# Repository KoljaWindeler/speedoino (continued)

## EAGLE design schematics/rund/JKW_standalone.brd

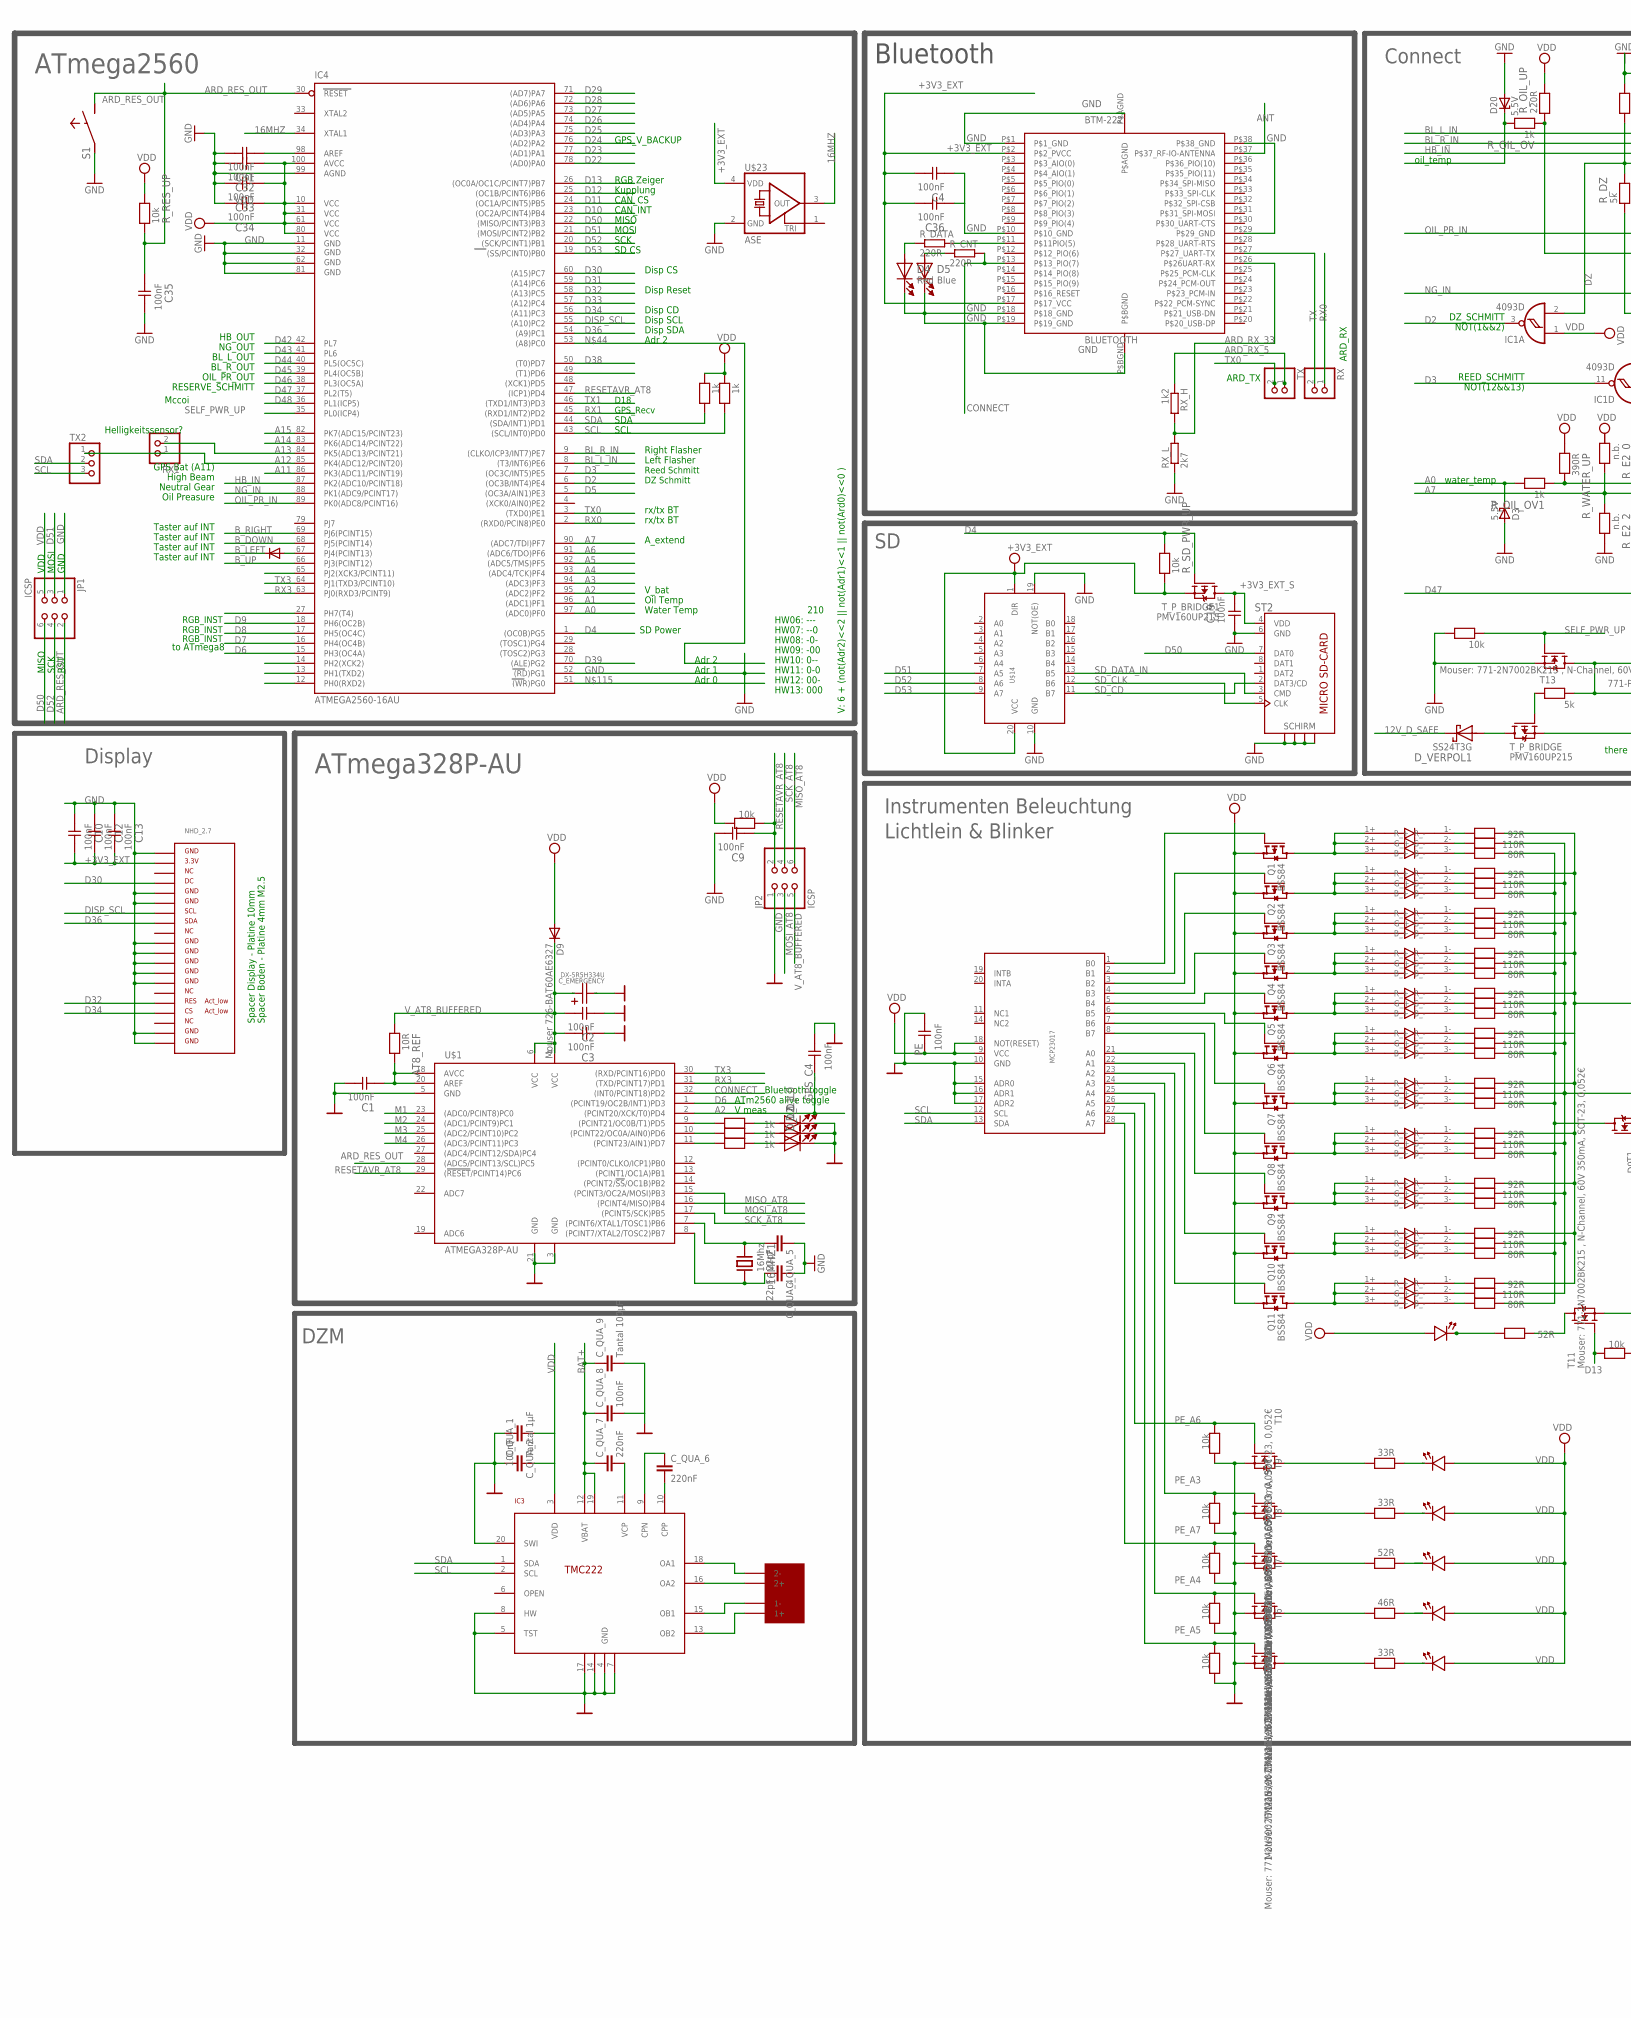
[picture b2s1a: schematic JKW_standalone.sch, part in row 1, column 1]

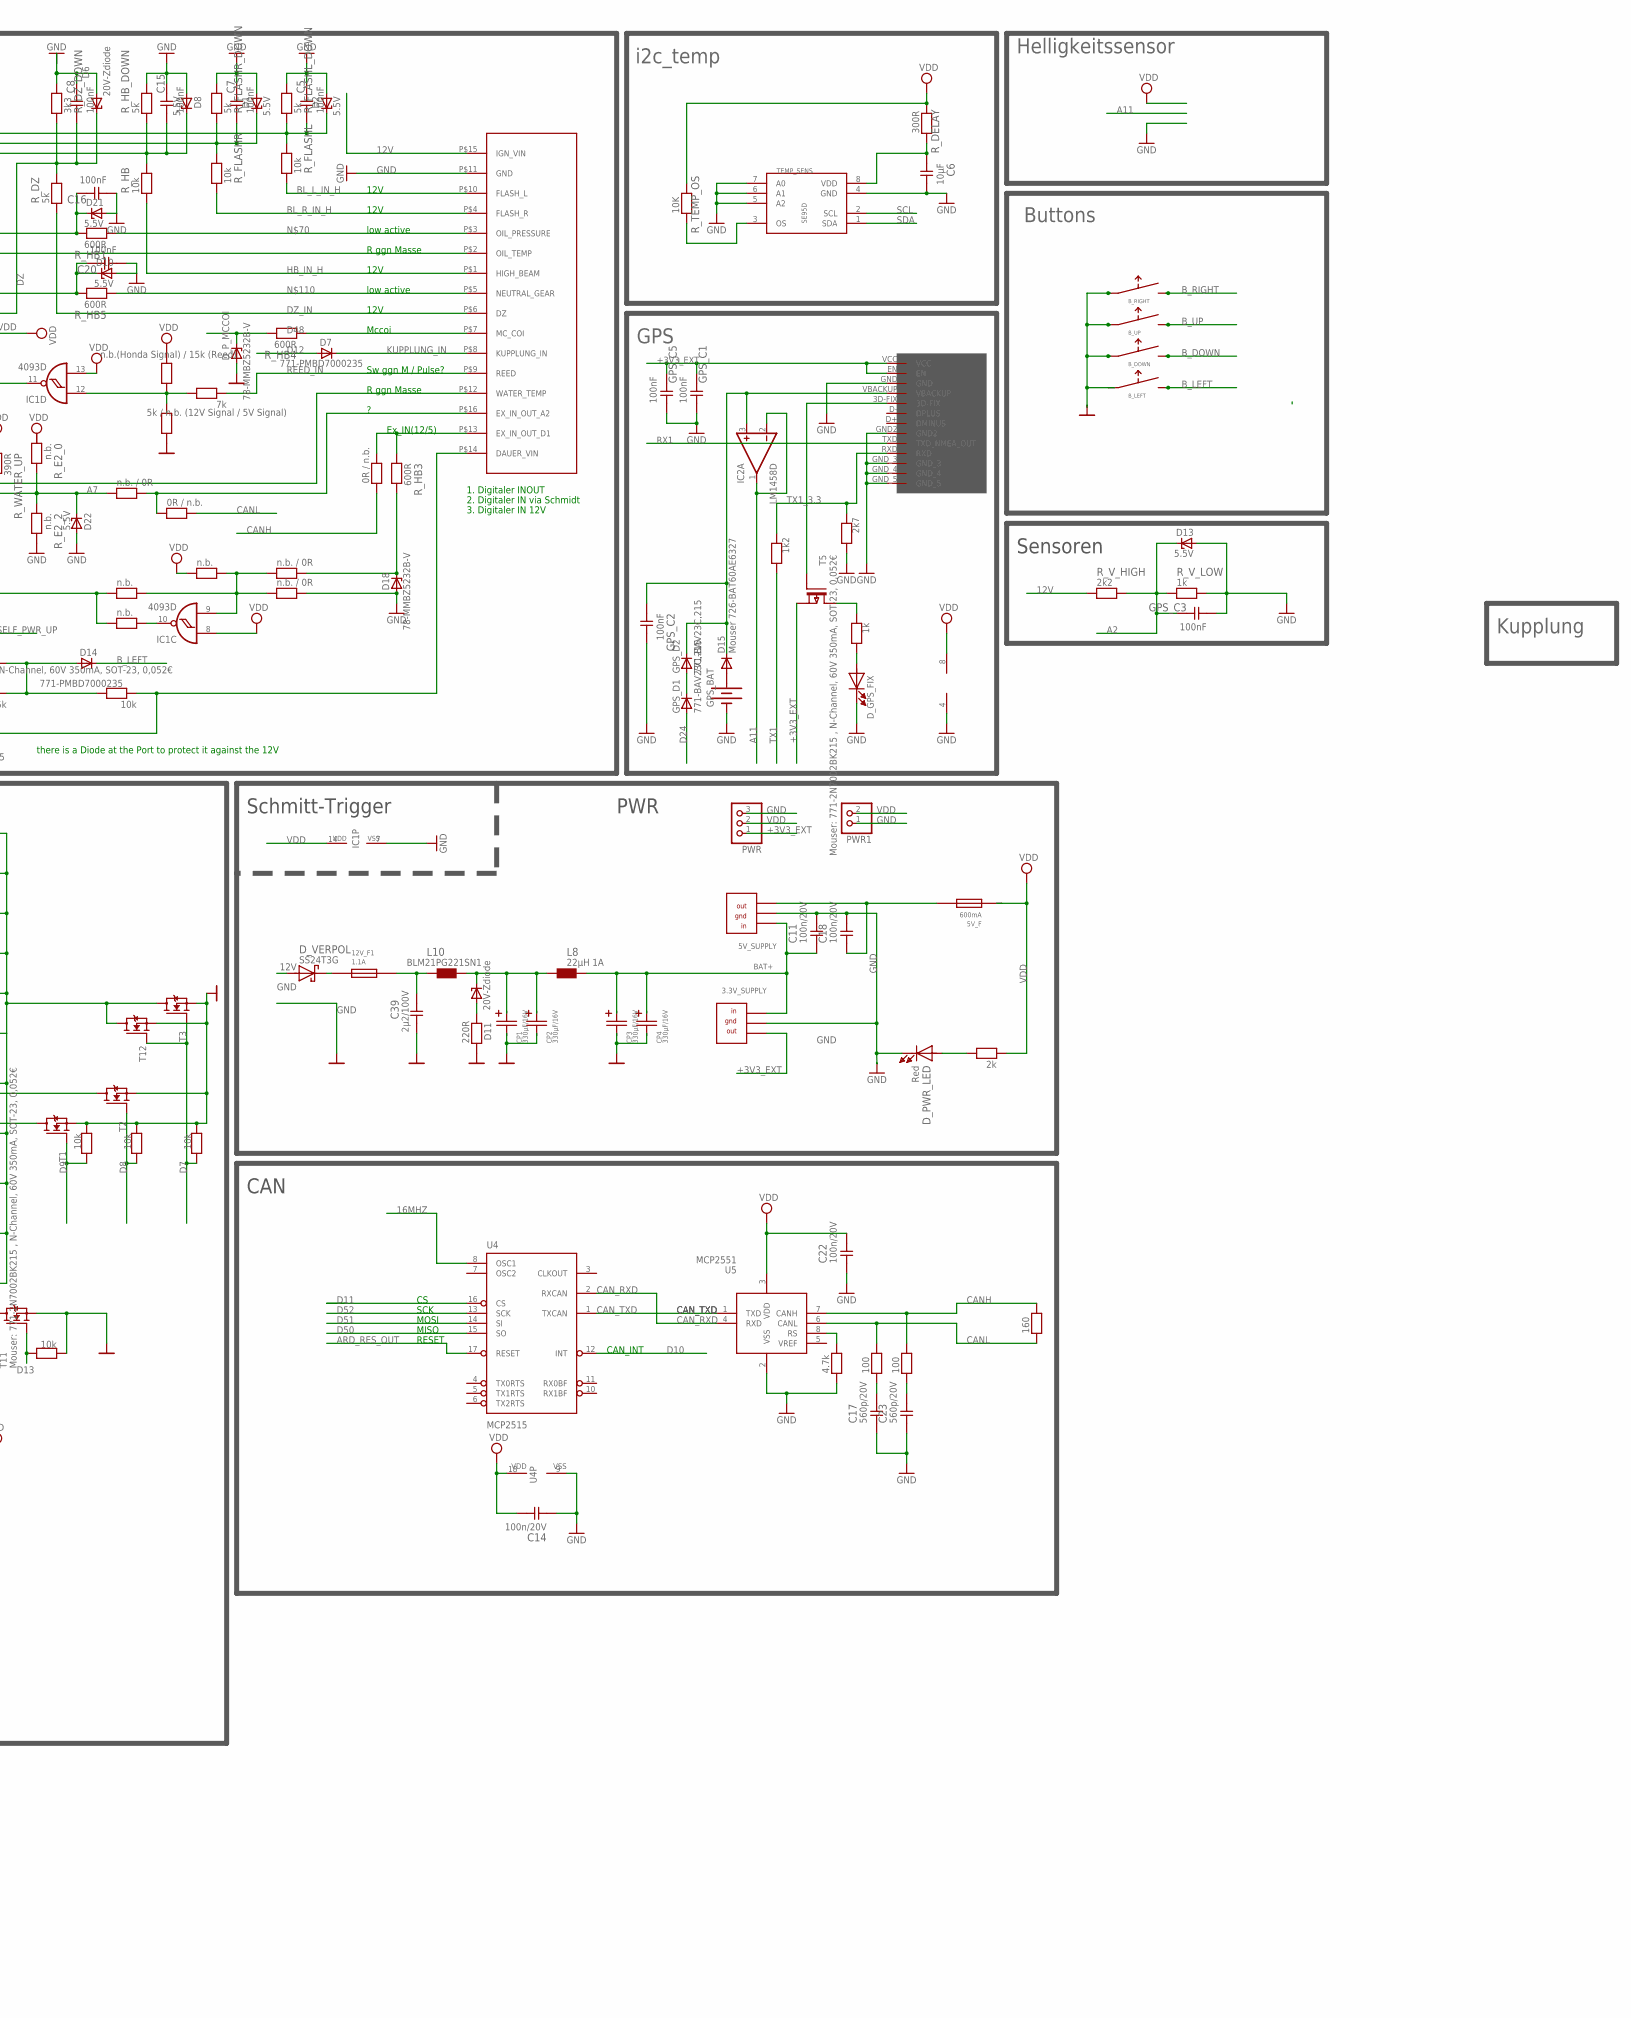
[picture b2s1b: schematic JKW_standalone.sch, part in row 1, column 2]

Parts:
3.3V_SUPPLY: OKI78SR3.31.5WHC; OKI-78SR
5V_F: 600mA; POLY_FUSE
5V_SUPPLY: OKI78SR51.5W36HC; OKI-78SR
12V_F1: 1.1A; POLY_FUSE
16MHZ1: 16Mhz; XT-HC49S-SMD
AT8_REF: 10R; 0805
BLUETOOTH: BTM-222
B_DOWN: SMD_TASTER_MIT_KAPPE; SMD_DRUCKTASTER
B_LEFT: SMD_TASTER_MIT_KAPPE; SMD_DRUCKTASTER
B_RIGHT: SMD_TASTER_MIT_KAPPE; SMD_DRUCKTASTER
B_UP: SMD_TASTER_MIT_KAPPE; SMD_DRUCKTASTER
C1, C2, C3, C4, C5, C7, C8, C9, C10, C12, C13, C15, C16, C19, C20, C31, C32, C33, C34, C35, C36: 100nF; 0805
C6: 10µF; 0805
C11, C14, C18, C22: 100n/20V; 0805
C17, C23: 560p/20V; 0805
C39: 2µ2/100V; 0805
CP1, CP2, CP3, CP4: 330µF/16V; SMD/SMT_6.6/6.6
C_EMERGENCY: DX-5R5H334U; GOLDCAP
C_QUA_1: Tantal 1µF; C0805
C_QUA_2, C_QUA_8: 100nF; C0805
C_QUA_4, C_QUA_5: 22pF; C0805
C_QUA_6, C_QUA_7: 220nF; C0805
C_QUA_9: Tantal 100µF; C0805
D1, D2, D3, D8, D10, D13, D20, D21, D22: 5.5V; SOT23
D4: Red; LED-0805
D5: Blue; LED-0805
D6, D11: 20V-Zdiode; SOT23
D7, D12, D14: 771-PMBD7000235; SOT23
D9, D15: Mouser 726-BAT60AE6327; SOD323-W
D18: 78-MMBZ5232B-V; SOT23
D_GPS_FIX: Red; LED-0805
D_GR_BLR: PLCC4_LED; PLCC-4
D_GR_N: PLCC4_LED; PLCC-4
D_L0, D_L1, D_L2: LED0805; LED-0805
D_PWR_LED: Red; LED-0805
D_P_MCCOI: 78-MMBZ5232B-V; SOT23
D_VERPOL, D_VERPOL1: SS24T3G; SMB
GPS: MT3329
GPS_BAT: F_908642; BATTCON_12MM
GPS_C1, GPS_C2, GPS_C3, GPS_C4, GPS_C5: 100nF; 0805
GPS_D1, GPS_D2: 771-BAV23C,215; SOT23
IC1: 4093D; SO14
IC2: LM1458D; SO08
IC3: TMC222; SOIC20
IC4: ATMEGA2560-16AU; TQFP100
JP1, JP2: ICSP; 2X03
L8: 22µH 1A; L-PD54
L10: BLM21PG221SN1; 0805+603
NHD_2.7: NHD_2.7_SOLO_RO
PE: 100nF; 0805
PWR: PINHD-1X3; 1X03
PWR1: PINHD-1X2; 1X02
Q1, Q2, Q3, Q4, Q5, Q6, Q7, Q8, Q9, Q10, Q11: BSS84; SOT23
R1: 160; 0805
R10, R12: 100; 0805
R13: 4.7k; 0805
RGB_1, RGB_2, RGB_3, RGB_4, RGB_5, RGB_6, RGB_7, RGB_8, RGB_9, RGB_10, RGB_11: RGB_LED; PLCC-6
RX, RX1: PINHD-1X2; 1X02
RX_H: 1k2; M0805
RX_L: 2k7; M0805
R_BL_L: 33R; 0805
R_BL_R: 33R; 0805
R_B_LED_1, R_B_LED_2, R_B_LED_3, R_B_LED_4, R_B_LED_5, R_B_LED_6, R_B_LED_7, R_B_LED_8, R_B_LED_9, R_B_LED_10, R_B_LED_11: 80R; 0805
R_B_LED_12, R_B_LED_13, R_B_LED_14, R_B_LED_15, R_B_LED_16, R_B_LED_17, R_B_LED_18, R_B_LED_19, R_B_LED_20: 10k; 0805
R_CNT: 220R; M0805
R_DATA: 220R; M0805
R_DEAKT_DAUER_P, R_DEAKT_DAUER_P1: 10k; 0805
R_DEAKT_DAUER_P2: 5k; 0805
R_DELAY: 300R; 0805
R_DZ: 5k; 0805
R_DZ_DOWN: 3k3; 0805
R_E1_0, R_E1_2, R_E1_4, R_E2_0, R_E2_2: n.b.; 0805
R_E1_1, R_E1_3, R_E2_1: n.b. / 0R; 0805
R_E2_3, R_E2_4: 0R / n.b.; 0805
R_FLASHL: 10k; 0805
R_FLASHL_DOWN: 5k; 0805
R_FLASHR: 10k; 0805
R_FLASHR_DOWN: 5k; 0805
R_GPS_LED: 1k; 0805
R_GR_BL_L: PLCC4_LED; PLCC-4
R_G_LED_1, R_G_LED_2, R_G_LED_3, R_G_LED_4, R_G_LED_5, R_G_LED_6, R_G_LED_7, R_G_LED_8, R_G_LED_9, R_G_LED_10, R_G_LED_11: 110R; 0805
R_HB: 10k; 0805
R_HB1, R_HB3, R_HB4, R_HB5: 600R; 0805
R_HB_DOWN: 5k; 0805
R_HIGHB: 46R; 0805
R_L0, R_L1, R_L2: 1k; 0805
R_L3: 10k; 0805
R_LED_5V: 2k; 0805
R_N: 33R; 0805
R_OIL: 52R; 0805
R_OIL_OV, R_OIL_OV1: 1k; 0805
R_OIL_UP: 220R; 0805
R_REED: 7k; 0805
R_REED_DOWN: 5k / n.b. (12V Signal / 5V Signal); 0805
R_REED_UP: n.b.(Honda Signal) / 15k (Reed); 0805
R_RES_UP: 10k; 0805
R_R_LED_0: 52R; 0805
R_R_LED_1, R_R_LED_2, R_R_LED_3, R_R_LED_4, R_R_LED_5, R_R_LED_6, R_R_LED_7, R_R_LED_8, R_R_LED_9, R_R_LED_10, R_R_LED_11: 92R; 0805
R_R_LED_12: 220R; 0805
R_SCL_UP: 1k; 0805
R_SDA_UP: 1k; 0805
R_SD_PWR_UP: 10k; 0805
R_TEMP_OS: 10K; 0805
R_TX_DOWN: 2k7; 0805
R_TX_UP: 1k2; 0805
R_V_HIGH: 2k2; 0805
R_V_LOW: 1k; 0805
R_WATER_UP: 390R; 0805
S1: SW-TASTERECO-DIAGONAL; SW-ECO
SPEEDOSTECKER: SPEEDOSTECKER
ST2: SD_MICRO
STEPPER: STEPPER
T1, T2, T3, T6, T7, T8, T9, T10, T11, T12, T13: Mouser: 771-2N7002BK215 , N-Channel, 60V 350mA, S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; SOT23
T5: Mouser: 771-2N7002BK215 , N-Channel, 60V 350mA, S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; SOT-23
TEMP_SENS: SE95D; SOIC8
TX: PINHD-1X2; 1X02
TX2: PINHD-1X3; 1X03
T_P_BRIDGE, T_P_BRIDGE1: PMV160UP215; SOT23
U4: MCP2515; SO-18W
U5: MCP2551; SO-08M
U$1: ATMEGA328P-AU; TQFP8
U$3: CLM4B-BKW-CTBVA363; PLCC-4
U$11, U$22: CLM4B-RKW-CWAXBAA3; PLCC-4
U$14: 74LVC_LVCH245A; TSSOP20
U$19: MCP23017; SOIC28
U$23: ASE

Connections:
3D-FIX: GPS.3D-FIX, T5.1 (G)
12V: D_VERPOL.A, R_V_HIGH.1, SPEEDOSTECKER.P$15 (IGN_VIN)
12V_D_SAFE: 12V_F1.P$1, D_VERPOL.K, D_VERPOL1.K
12V_PERMANENT: R_DEAKT_DAUER_P.1, SPEEDOSTECKER.P$14 (DAUER_VIN), T_P_BRIDGE.2 (S)
12V_SAFE: 12V_F1.P$2, C39.1, L10.1
16MHZ: IC4.34 (XTAL1), U4.8 (OSC1), U$23.3 (OUT)
+3V3_EXT: 3.3V_SUPPLY.OUT, BLUETOOTH.P$2 (P$2_PVCC), BLUETOOTH.P$17 (P$17_VCC), C4.2, C10.2, C12.2, C13.2, C36.2, GPS.EN, GPS.VCC, GPS_C1.2, GPS_C5.2, NHD_2.7.VDD0 (VDD), PWR.1, R_SD_PWR_UP.1, T5.2 (S), T_P_BRIDGE1.2 (S), U$14.1 (DIR), U$14.20 (VCC)
+3V3_EXT_S: C19.2, ST2.4 (VDD), T_P_BRIDGE1.3 (D)
A0: D3.3 (C), IC4.97 ((ADC0)PF0), R_OIL_OV1.2
A1: D20.3 (C), IC4.96 ((ADC1)PF1), R_OIL_OV.2
A2: D13.3 (C), GPS_C3.2, GPS_C4.2, IC4.95 ((ADC2)PF2), R_V_HIGH.2, R_V_LOW.1, U$1.2 ((PCINT20/XCK/T0)PD4)
A3: IC4.94 ((ADC3)PF3)
A4: IC4.93 ((ADC4/TCK)PF4)
A5: IC4.92 ((ADC5/TMS)PF5)
A6: IC4.91 ((ADC6/TDO)PF6)
A7: D22.3 (C), IC4.90 ((ADC7/TDI)PF7), R_E2_0.2, R_E2_1.2, R_E2_2.1
A11: IC2.1 (OUT), IC2.2 (-IN), IC4.86 (PK3(ADC11/PCINT19))
A12: IC4.85 (PK4(ADC12/PCINT20)), RX1.1, TX2.1
A13: IC4.84 (PK5(ADC13/PCINT21)), RX1.2
A14: IC4.83 (PK6(ADC14/PCINT22))
A15: IC4.82 (PK7(ADC15/PCINT23))
ANT: BLUETOOTH.P$37 (P$37_RF-IO-ANTENNA)
ARD_RES_OUT: C35.1, IC4.30 (RESET), JP1.2, R_RES_UP.1, S1.4 (2), U4.17 (RESET), U$1.28 ((ADC5/PCINT13/SCL)PC5)
ARD_RX_5: RX_H.1, TX.1
ARD_RX_33: BLUETOOTH.P$26 (P$26UART-RX), RX_H.2, RX_L.2
BAT+: 3.3V_SUPPLY.IN, 5V_SUPPLY.IN, C11.1, CP3.POS (PLUS), CP4.POS (PLUS), C_QUA_7.1, C_QUA_8.1, C_QUA_9.1, IC3.12 (VBAT), IC3.19 (VBAT2), L8.2
BLUE_INSTR: R_B_LED_1.2, R_B_LED_2.2, R_B_LED_3.2, R_B_LED_4.2, R_B_LED_5.2, R_B_LED_6.2, R_B_LED_7.2, R_B_LED_8.2, R_B_LED_9.2, R_B_LED_10.2, R_B_LED_11.2, T1.3 (D)
BL_L_IN: C5.1, D2.3 (C), IC4.8 ((T3/INT6)PE6), R_FLASHL.2, R_FLASHL_DOWN.1
BL_L_IN_H: R_FLASHL.1, SPEEDOSTECKER.P$10 (FLASH_L)
BL_R_IN: C7.1, D1.3 (C), IC4.9 ((CLKO/ICP3/INT7)PE7), R_FLASHR.2, R_FLASHR_DOWN.1
BL_R_IN_H: R_FLASHR.1, SPEEDOSTECKER.P$4 (FLASH_R)
B_DOWN: B_DOWN.OUT, IC4.68 (PJ5(PCINT14))
B_LEFT: B_LEFT.OUT, D12.3 (C), D14.3 (C)
B_RIGHT: B_RIGHT.OUT, IC4.69 (PJ6(PCINT15))
B_UP: B_UP.OUT, IC4.66 (PJ3(PCINT12))
CANH: R1.2, R12.2, R_E2_4.2, U5.7 (CANH)
CANL: R1.1, R10.2, R_E2_3.1, U5.6 (CANL)
CAN_RXD: U4.2 (RXCAN), U5.4 (RXD)
CAN_TXD: U4.1 (TXCAN), U5.1 (TXD)
CONNECT: BLUETOOTH.P$13 (P$13_PIO(7)), R_CNT.2, U$1.32 ((INT0/PCINT18)PD2)
D2: IC1.3 (O), IC4.6 ((OC3B/INT4)PE4)
D3: IC1.11 (O), IC4.7 ((OC3C/INT5)PE5)
D4: IC4.1 ((OC0B)PG5), R_SD_PWR_UP.2, T_P_BRIDGE1.1 (G)
D5: IC4.5 ((OC3A/AIN1)PE3)
D6: IC4.15 (PH3(OC4A)), U$1.1 ((PCINT19/OC2B/INT1)PD3)
D7: IC4.16 (PH4(OC4B)), R_B_LED_15.1, T3.1 (G), T12.1 (G)
D8: IC4.17 (PH5(OC4C)), R_B_LED_14.1, T2.1 (G)
D9: IC4.18 (PH6(OC2B)), R_B_LED_13.1, T1.1 (G)
D10: IC4.23 ((OC2A/PCINT4)PB4), U4.12 (INT)
D11: IC4.24 ((OC1A/PCINT5)PB5), U4.16 (CS)
D12: D7.1 (A), IC4.25 ((OC1B/PCINT6)PB6)
D13: IC4.26 ((OC0A/OC1C/PCINT7)PB7), R_B_LED_12.1, T11.1 (G)
D22: IC4.78 ((AD0)PA0)
D23: IC4.77 ((AD1)PA1)
D24: GPS_D1.1 (A), IC4.76 ((AD2)PA2)
D25: IC4.75 ((AD3)PA3)
D26: IC4.74 ((AD4)PA4)
D27: IC4.73 ((AD5)PA5)
D28: IC4.72 ((AD6)PA6)
D29: IC4.71 ((AD7)PA7)
D30: IC4.60 ((A15)PC7), NHD_2.7.DC
D31: IC4.59 ((A14)PC6)
D32: IC4.58 ((A13)PC5), NHD_2.7.RES
D33: IC4.57 ((A12)PC4)
D34: IC4.56 ((A11)PC3), NHD_2.7.CS
D36: IC4.54 ((A9)PC1), NHD_2.7.SDIN (SDA)
D38: IC4.50 ((T0)PD7)
D39: IC4.70 ((ALE)PG2)
D42: IC4.42 (PL7)
D43: IC4.41 (PL6)
D44: IC4.40 (PL5(OC5C))
D45: IC4.39 (PL4(OC5B))
D46: IC4.38 (PL3(OC5A))
D47: IC4.37 (PL2(T5)), R_E1_2.2, R_E1_4.2
D48: D_P_MCCOI.3 (C), IC4.36 (PL1(ICP5)), R_HB4.2
D50: IC4.22 ((MISO/PCINT3)PB3), JP1.6, ST2.7 (DAT0), U4.15 (SO)
D51: IC4.21 ((MOSI/PCINT2)PB2), JP1.3, U4.14 (SI), U$14.7 (A5)
D52: IC4.20 ((SCK/PCINT1)PB1), JP1.4, U4.13 (SCK), U$14.8 (A6)
D53: IC4.19 ((SS/PCINT0)PB0), U$14.9 (A7)
DISP_SCL: IC4.55 ((A10)PC2), NHD_2.7.SCLK (SCL)
DZ: C8.1, D6.3 (C), IC1.2 (I1), R_DZ.2, R_DZ_DOWN.1
DZ_IN: R_DZ.1, SPEEDOSTECKER.P$6 (DZ)
GND: 3.3V_SUPPLY.GND, 5V_SUPPLY.GND, BLUETOOTH.P$1 (P$1_GND), BLUETOOTH.P$10 (P$10_GND), BLUETOOTH.P$18 (P$18_GND), BLUETOOTH.P$19 (P$19_GND), BLUETOOTH.P$29 (P$29_GND), BLUETOOTH.P$38 (P$38_GND), BLUETOOTH.P$AGND, BLUETOOTH.P$BGND, B_DOWN.IN, B_DOWN.IN2 (IN), B_LEFT.IN, B_LEFT.IN2 (IN), B_RIGHT.IN, B_RIGHT.IN2 (IN), B_UP.IN, B_UP.IN2 (IN), C1.2, C2.1, C3.1, C4.1, C5.2, C6.2, C7.2, C8.2, C9.2, C10.1, C11.2, C12.1, C13.1, C14.1, C15.2, C16.1, C17.1, C18.2, C19.1, C20.1, C22.1, C23.1, C31.2, C32.2, C33.2, C34.2, C35.2, C36.1, C39.2, CP1.NEG (GND), CP2.NEG (GND), CP3.NEG (GND), CP4.NEG (GND), C_EMERGENCY.MINUS (GND), C_QUA_1.1, C_QUA_2.2, C_QUA_4.1, C_QUA_5.1, C_QUA_8.2, C_QUA_9.2, D1.1 (A), D2.1 (A), D3.1 (A), D4.2 (K), D5.2 (K), D6.1 (A), D8.1 (A), D10.1 (A), D13.1 (A), D18.1 (A), D20.1 (A), D21.1 (A), D22.1 (A), D_GPS_FIX.2 (K), D_L0.2 (K), D_L1.2 (K), D_L2.2 (K), D_PWR_LED.2 (K), D_P_MCCOI.1 (A), GPS.GND, GPS.GND2, GPS.GND_3, GPS.GND_4, GPS.GND_5, GPS_BAT.GND (-), GPS_C1.1, GPS_C2.2, GPS_C3.1, GPS_C4.1, GPS_C5.1, IC1.7 (VSS), IC2.4 (V-), IC3.4 (GND), IC3.5 (TST), IC3.7 (GND2), IC3.8 (HW), IC3.14 (GND3), IC3.17 (GND4), IC3.20 (SWI), IC4.11 (GND), IC4.32 (GND1), IC4.52 ((RD)PG1), IC4.62 (GND2), IC4.81 (GND3), IC4.99 (AGND), JP1.1, JP2.1, NHD_2.7.GND0 (GND), NHD_2.7.GND1 (GND2), NHD_2.7.GND2 (GND3), NHD_2.7.GND3 (GND4), NHD_2.7.GND4 (GND5), NHD_2.7.GND5 (GND6), NHD_2.7.GND6 (GND7), NHD_2.7.GND7 (GND8), NHD_2.7.GND8 (GND9), NHD_2.7.GND9 (GND10), PE.1, PWR.3, PWR1.1, R13.1, RX_L.1, R_B_LED_12.2, R_B_LED_13.2, R_B_LED_14.2, R_B_LED_15.2, R_B_LED_16.1, R_B_LED_17.1, R_B_LED_18.1, R_B_LED_19.1, R_B_LED_20.1, R_DEAKT_DAUER_P1.2, R_DZ_DOWN.2, R_E1_3.1, R_E2_2.2, R_FLASHL_DOWN.2, R_FLASHR_DOWN.2, R_HB_DOWN.2, R_REED_DOWN.2, R_R_LED_12.1, R_TX_DOWN.2, R_V_LOW.2, S1.1, SPEEDOSTECKER.P$11 (GND), ST2.6 (GND), ST2.GND (SCHIRM1), ST2.GND2 (SCHIRM2), ST2.GND3 (SCHIRM3), ST2.GND4 (SCHIRM), T1.2 (S), T2.2 (S), T3.2 (S), T6.2 (S), T7.2 (S), T8.2 (S), T9.2 (S), T10.2 (S), T11.2 (S), T12.2 (S), T13.2 (S), TEMP_SENS.4 (GND), TEMP_SENS.5 (A2), TEMP_SENS.6 (A1), TEMP_SENS.7 (A0), U4.9 (VSS), U5.2 (VSS), U$1.3 (GND), U$1.5 (GND), U$1.21 (GND), U$14.10 (GND), U$14.19 (NOT(OE)), U$19.10 (GND), U$19.15 (ADR0), U$19.16 (ADR1), U$19.17 (ADR2), U$23.2 (GND)
GREEN_INSTR: R_G_LED_1.2, R_G_LED_2.2, R_G_LED_3.2, R_G_LED_4.2, R_G_LED_5.2, R_G_LED_6.2, R_G_LED_7.2, R_G_LED_8.2, R_G_LED_9.2, R_G_LED_10.2, R_G_LED_11.2, T2.3 (D)
HB_IN: C15.1, D8.3 (C), IC4.87 (PK2(ADC10/PCINT18)), R_HB.2, R_HB_DOWN.1
HB_IN_H: R_HB.1, SPEEDOSTECKER.P$1 (HIGH_BEAM)
KUPPLUNG_IN: D7.3 (C), SPEEDOSTECKER.P$8 (KUPPLUNG_IN)
M1: U$1.23 ((ADC0/PCINT8)PC0)
M2: U$1.24 ((ADC1/PCINT9)PC1)
M3: U$1.25 ((ADC2/PCINT10)PC2)
M4: U$1.26 ((ADC3/PCINT11)PC3)
MISO_AT8: JP2.6, U$1.16 ((PCINT4/MISO)PB4)
MOSI_AT8: JP2.3, U$1.15 ((PCINT3/OC2A/MOSI)PB3)
N999: R_OIL_OV.1, R_OIL_UP.1, SPEEDOSTECKER.P$2 (OIL_TEMP)
unnamed: CP1.POS (PLUS), CP2.POS (PLUS), D11.3 (C), L8.1, L10.2
unnamed: AT8_REF.2, C1.1, U$1.18 (AVCC), U$1.20 (AREF)
unnamed: C6.1, R_DELAY.1, TEMP_SENS.8 (VDD)
unnamed: D5.1 (A), R_CNT.1
unnamed: RGB_5.3- (B_-), R_B_LED_4.1
unnamed: RGB_5.2- (G_-), R_G_LED_4.1
unnamed: RGB_5.1- (R_-), R_R_LED_4.1
unnamed: D_PWR_LED.1 (A), R_LED_5V.2
unnamed: RGB_6.3- (B_-), R_B_LED_5.1
unnamed: D15.A, GPS_BAT.PWR@1 (+)
unnamed: D4.1 (A), R_DATA.1
unnamed: Q11.3 (D), RGB_11.1+ (R_+), RGB_11.2+ (G_+), RGB_11.3+ (B_+)
unnamed: R_L2.1, U$1.11 ((PCINT23/AIN1)PD7)
unnamed: D_GPS_FIX.1 (A), R_GPS_LED.2
unnamed: R_R_LED_0.1, U$22.P$4 (CATHODE)
unnamed: R_GPS_LED.1, T5.3 (D)
unnamed: R_L1.1, U$1.10 ((PCINT22/OC0A/AIN0)PD6)
unnamed: 5V_F.P$2, 5V_SUPPLY.OUT, C18.1
unnamed: R_L0.1, U$1.9 ((PCINT21/OC0B/T1)PD5)
unnamed: RGB_6.2- (G_-), R_G_LED_5.1
unnamed: RGB_6.1- (R_-), R_R_LED_5.1
unnamed: Q10.3 (D), RGB_10.1+ (R_+), RGB_10.2+ (G_+), RGB_10.3+ (B_+)
unnamed: R_DEAKT_DAUER_P2.2, T_P_BRIDGE.1 (G)
unnamed: R_OIL.1, U$11.P$4 (CATHODE)
unnamed: Q9.3 (D), RGB_1.1+ (R_+), RGB_1.2+ (G_+), RGB_1.3+ (B_+)
unnamed: RGB_7.3- (B_-), R_B_LED_6.1
unnamed: R_HIGHB.1, U$3.P$4 (CATHODE)
unnamed: RGB_7.2- (G_-), R_G_LED_6.1
unnamed: RGB_7.1- (R_-), R_R_LED_6.1
unnamed: R_BL_L.2, T10.3 (D)
unnamed: R_BL_R.2, T9.3 (D)
unnamed: IC3.18 (OA1), STEPPER.2-
unnamed: IC3.16 (OA2), STEPPER.2+
unnamed: C31.1, IC4.98 (AREF)
unnamed: IC1.9 (I1), R_E1_0.1, R_E1_1.2, R_E1_2.1, R_E1_3.2
unnamed: R_HIGHB.2, T7.3 (D)
unnamed: IC1.10 (O), R_E1_4.1
unnamed: D12.1 (A), IC4.67 (PJ4(PCINT13))
unnamed: R_E2_4.1, R_HB3.1, SPEEDOSTECKER.P$13 (EX_IN_OUT_D1)
unnamed: R_E2_1.1, R_E2_3.2, SPEEDOSTECKER.P$16 (EX_IN_OUT_A2)
unnamed: D_VERPOL1.A, T_P_BRIDGE.3 (D)
unnamed: C17.2, R10.1
unnamed: GPS_D1.3 (C), GPS_D2.1 (A)
unnamed: IC3.13 (OB2), STEPPER.1+
unnamed: RGB_4.1- (R_-), R_R_LED_3.1
unnamed: RGB_4.2- (G_-), R_G_LED_3.1
unnamed: RGB_4.3- (B_-), R_B_LED_3.1
unnamed: RGB_3.1- (R_-), R_R_LED_2.1
unnamed: RGB_3.2- (G_-), R_G_LED_2.1
unnamed: RGB_3.3- (B_-), R_B_LED_2.1
unnamed: RGB_2.1- (R_-), R_R_LED_1.1
unnamed: RGB_2.2- (G_-), R_G_LED_1.1
unnamed: RGB_2.3- (B_-), R_B_LED_1.1
unnamed: R_BL_L.1, R_GR_BL_L.P$4 (CATHODE)
unnamed: 16MHZ1.1, C_QUA_5.2, U$1.7 ((PCINT6/XTAL1/TOSC1)PB6)
unnamed: RGB_11.1- (R_-), R_R_LED_7.1
unnamed: 16MHZ1.2, C_QUA_4.2, U$1.8 ((PCINT7/XTAL2/TOSC2)PB7)
unnamed: D_GR_BLR.P$4 (CATHODE), R_BL_R.1
unnamed: R_N.2, T6.3 (D)
unnamed: R_OIL.2, T8.3 (D)
unnamed: D_GR_N.P$4 (CATHODE), R_N.1
unnamed: R_HB1.1, SPEEDOSTECKER.P$3 (OIL_PRESSURE)
unnamed: R_R_LED_0.2, T11.3 (D)
unnamed: RGB_11.2- (G_-), R_G_LED_7.1
unnamed: RGB_11.3- (B_-), R_B_LED_7.1
unnamed: RGB_10.1- (R_-), R_R_LED_8.1
unnamed: RGB_10.2- (G_-), R_G_LED_8.1
unnamed: RGB_10.3- (B_-), R_B_LED_8.1
unnamed: RGB_9.1- (R_-), R_R_LED_9.1
unnamed: RGB_9.2- (G_-), R_G_LED_9.1
unnamed: RGB_9.3- (B_-), R_B_LED_9.1
unnamed: RGB_8.1- (R_-), R_R_LED_10.1
unnamed: RGB_8.2- (G_-), R_G_LED_10.1
unnamed: RGB_8.3- (B_-), R_B_LED_10.1
unnamed: RGB_1.1- (R_-), R_R_LED_11.1
unnamed: RGB_1.2- (G_-), R_G_LED_11.1
unnamed: RGB_1.3- (B_-), R_B_LED_11.1
unnamed: Q8.3 (D), RGB_8.1+ (R_+), RGB_8.2+ (G_+), RGB_8.3+ (B_+)
unnamed: Q7.3 (D), RGB_9.1+ (R_+), RGB_9.2+ (G_+), RGB_9.3+ (B_+)
unnamed: Q1.3 (D), RGB_7.1+ (R_+), RGB_7.2+ (G_+), RGB_7.3+ (B_+)
unnamed: C23.2, R12.1
unnamed: D18.3 (C), R_E1_1.1, R_HB3.2
unnamed: R_TEMP_OS.1, TEMP_SENS.3 (OS)
unnamed: R_HB4.1, SPEEDOSTECKER.P$7 (MC_COI)
unnamed: Q2.3 (D), RGB_6.1+ (R_+), RGB_6.2+ (G_+), RGB_6.3+ (B_+)
unnamed: Q3.3 (D), RGB_5.1+ (R_+), RGB_5.2+ (G_+), RGB_5.3+ (B_+)
unnamed: Q4.3 (D), RGB_4.1+ (R_+), RGB_4.2+ (G_+), RGB_4.3+ (B_+)
unnamed: Q6.3 (D), RGB_2.1+ (R_+), RGB_2.2+ (G_+), RGB_2.3+ (B_+)
unnamed: Q5.3 (D), RGB_3.1+ (R_+), RGB_3.2+ (G_+), RGB_3.3+ (B_+)
unnamed: Q1.1 (G), U$19.1 (B0)
unnamed: Q2.1 (G), U$19.2 (B1)
unnamed: Q3.1 (G), U$19.3 (B2)
unnamed: Q4.1 (G), U$19.4 (B3)
unnamed: Q5.1 (G), U$19.5 (B4)
unnamed: Q6.1 (G), U$19.6 (B5)
unnamed: Q7.1 (G), U$19.7 (B6)
unnamed: Q8.1 (G), U$19.8 (B7)
unnamed: Q9.1 (G), U$19.21 (A0)
unnamed: Q10.1 (G), U$19.22 (A1)
unnamed: Q11.1 (G), U$19.23 (A2)
unnamed: D11.1 (A), R_R_LED_12.2
unnamed: R_HB5.1, SPEEDOSTECKER.P$5 (NEUTRAL_GEAR)
unnamed: R_OIL_OV1.1, R_WATER_UP.2, SPEEDOSTECKER.P$12 (WATER_TEMP)
unnamed: R13.2, U5.8 (RS)
unnamed: IC3.15 (OB1), STEPPER.1-
unnamed: C_QUA_6.2, IC3.10 (CPP)
unnamed: C_QUA_6.1, IC3.9 (CPN)
unnamed: C_QUA_7.2, IC3.11 (VCP)
NET12: D14.1 (A), R_DEAKT_DAUER_P.2, R_DEAKT_DAUER_P2.1, T13.3 (D)
NG_IN: C20.2, D10.3 (C), IC4.88 (PK1(ADC9/PCINT17)), R_HB5.2
OIL_PR_IN: C16.2, D21.3 (C), IC4.89 (PK0(ADC8/PCINT16)), R_HB1.2
P0: D_L0.1 (A), R_L0.2
P1: D_L1.1 (A), R_L1.2
P2: D_L2.1 (A), R_L2.2
PE_A3: R_B_LED_17.2, T9.1 (G), U$19.24 (A3)
PE_A4: R_B_LED_19.2, T7.1 (G), U$19.25 (A4)
PE_A5: R_B_LED_20.2, T6.1 (G), U$19.26 (A5)
PE_A6: R_B_LED_16.2, T10.1 (G), U$19.27 (A6)
PE_A7: R_B_LED_18.2, T8.1 (G), U$19.28 (A7)
RED_INSTR: R_R_LED_1.2, R_R_LED_2.2, R_R_LED_3.2, R_R_LED_4.2, R_R_LED_5.2, R_R_LED_6.2, R_R_LED_7.2, R_R_LED_8.2, R_R_LED_9.2, R_R_LED_10.2, R_R_LED_11.2, T3.3 (D), T12.3 (D)
REED: IC1.12 (I0), R_REED.2, R_REED_DOWN.1, R_REED_UP.2
REED_IN: R_REED.1, SPEEDOSTECKER.P$9 (REED)
RESETAVR_AT8: C9.1, IC4.47 ((ICP1)PD4), JP2.2, R_L3.2, U$1.29 ((!RESET!/PCINT14)PC6)
RX0: IC4.2 ((RXD0/PCIN8)PE0), RX.1
RX1: GPS.TXD (TXD_NMEA_OUT), IC4.45 ((RXD1/INT2)PD2)
RX3: IC4.63 (PJ0(RXD3/PCINT9)), U$1.31 ((TXD/PCINT17)PD1)
SCK_AT8: JP2.4, U$1.17 ((PCINT5/SCK)PB5)
SCL: IC3.2 (SCL), IC4.43 ((SCL/INT0)PD0), R_SCL_UP.2, TEMP_SENS.2 (SCL), TX2.3, U$19.12 (SCL)
SDA: IC3.1 (SDA), IC4.44 ((SDA/INT1)PD1), R_SDA_UP.2, TEMP_SENS.1 (SDA), TX2.2, U$19.13 (SDA)
SD_CD: ST2.2 (DAT3/CD), U$14.11 (B7)
SD_CLK: ST2.5 (CLK), U$14.12 (B6)
SD_DATA_IN: ST2.3 (CMD), U$14.13 (B5)
SELF_PWR_UP: IC4.35 (PL0(ICP4)), R_DEAKT_DAUER_P1.1, T13.1 (G)
TO_DATA_LED: BLUETOOTH.P$11 (P$11PIO(5)), R_DATA.2
TX: BLUETOOTH.P$27 (P$27_UART-TX), RX.2
TX0: IC4.3 ((TXD0)PE1), TX.2
TX1: IC4.46 ((TXD1/INT3)PD3), R_TX_UP.2
TX1_3.3: GPS.RXD, R_TX_DOWN.1, R_TX_UP.1
TX3: IC4.64 (PJ1(TXD3/PCINT10)), U$1.30 ((RXD/PCINT16)PD0)
VDD: 5V_F.P$1, C14.2, C22.2, C32.1, C33.1, C34.1, C_QUA_1.2, C_QUA_2.1, D9.A, D_GR_BLR.P$1 (ANODE), D_GR_BLR.P$2 (ANODE), D_GR_BLR.P$3 (ANODE), D_GR_N.P$1 (ANODE), D_GR_N.P$2 (ANODE), D_GR_N.P$3 (ANODE), IC1.1 (I0), IC1.8 (I0), IC1.13 (I1), IC1.14 (VDD), IC2.8 (V+), IC3.3 (VDD), IC4.10 (VCC), IC4.31 (VCC1), IC4.61 (VCC2), IC4.80 (VCC3), IC4.100 (AVCC), JP1.5, PE.2, PWR.2, PWR1.2, Q1.2 (S), Q2.2 (S), Q3.2 (S), Q4.2 (S), Q5.2 (S), Q6.2 (S), Q7.2 (S), Q8.2 (S), Q9.2 (S), Q10.2 (S), Q11.2 (S), R_DELAY.2, R_E1_0.2, R_GR_BL_L.P$1 (ANODE), R_GR_BL_L.P$2 (ANODE), R_GR_BL_L.P$3 (ANODE), R_L3.1, R_LED_5V.1, R_OIL_UP.2, R_REED_UP.1, R_RES_UP.2, R_SCL_UP.1, R_SDA_UP.1, R_TEMP_OS.2, R_WATER_UP.1, U4.18 (VDD), U5.3 (VDD), U$3.P$1 (ANODE), U$3.P$2 (ANODE), U$3.P$3 (ANODE), U$11.P$1 (ANODE), U$11.P$2 (ANODE), U$11.P$3 (ANODE), U$19.9 (VCC), U$19.18 (NOT(RESET)), U$22.P$1 (ANODE), U$22.P$2 (ANODE), U$22.P$3 (ANODE), U$23.4 (VDD)
V_AT8_BUFFERED: AT8_REF.1, C2.2, C3.2, C_EMERGENCY.PLUS, D9.C, JP2.5, U$1.4 (VCC), U$1.6 (VCC)
V_BAT: D15.C, GPS.VBACKUP, GPS_C2.1, GPS_D2.3 (C), IC2.3 (+IN)

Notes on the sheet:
Schmitt-Trigger
PWR
Sensoren
Bluetooth
Buttons
MOSI
SCK
MISO
SDA
SCL
DZ_SCHMITT
REED_SCHMITT
oil_temp
ATmega2560
D18
GND
VDD
RST
ATm2560 alive toggle
ARD_RX
ARD_TX
i2c_temp
ATmega328P-AU
Lichtlein & Blinker
Instrumenten Beleuchtung
RGB_INST
Reed Schmitt
DZ Schmitt
GPS
GPS_Recv
Display
DZM
Oil Temp
rx/tx BT
Disp SDA
Disp SCL
Disp CD
Disp CS
SD CS
Water Temp

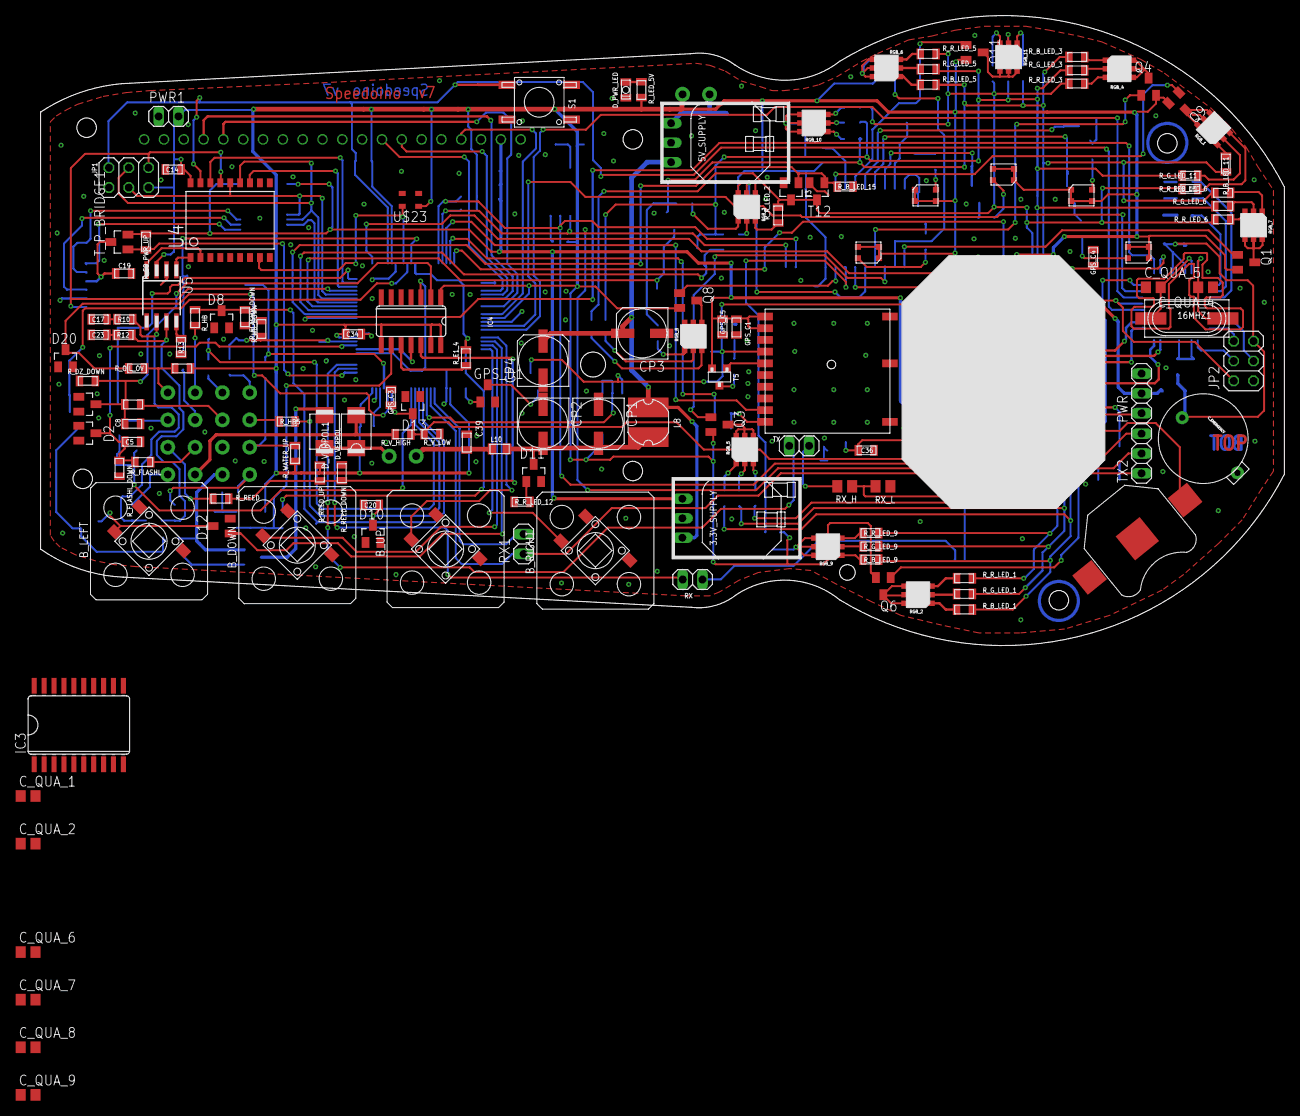
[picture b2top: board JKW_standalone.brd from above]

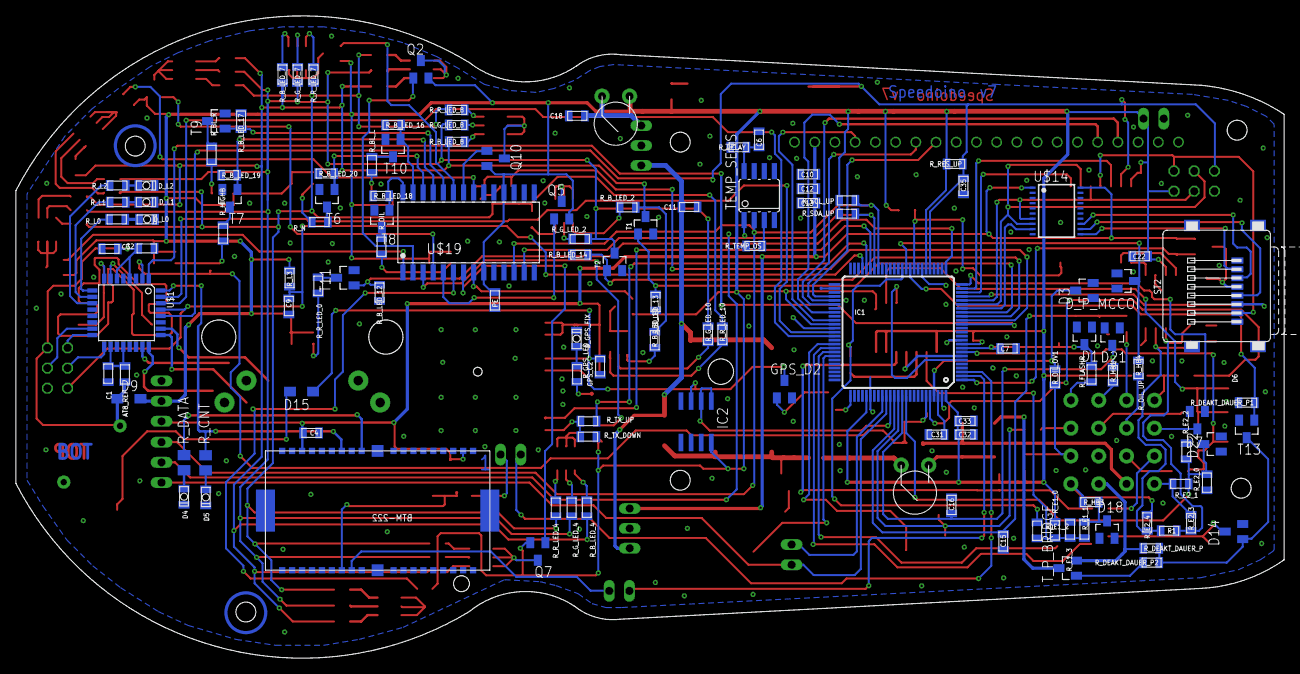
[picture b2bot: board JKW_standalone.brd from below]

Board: 2 copper layers, 159.4 x 80.7 mm, 263 parts (123 on the bottom side), 208 nets.

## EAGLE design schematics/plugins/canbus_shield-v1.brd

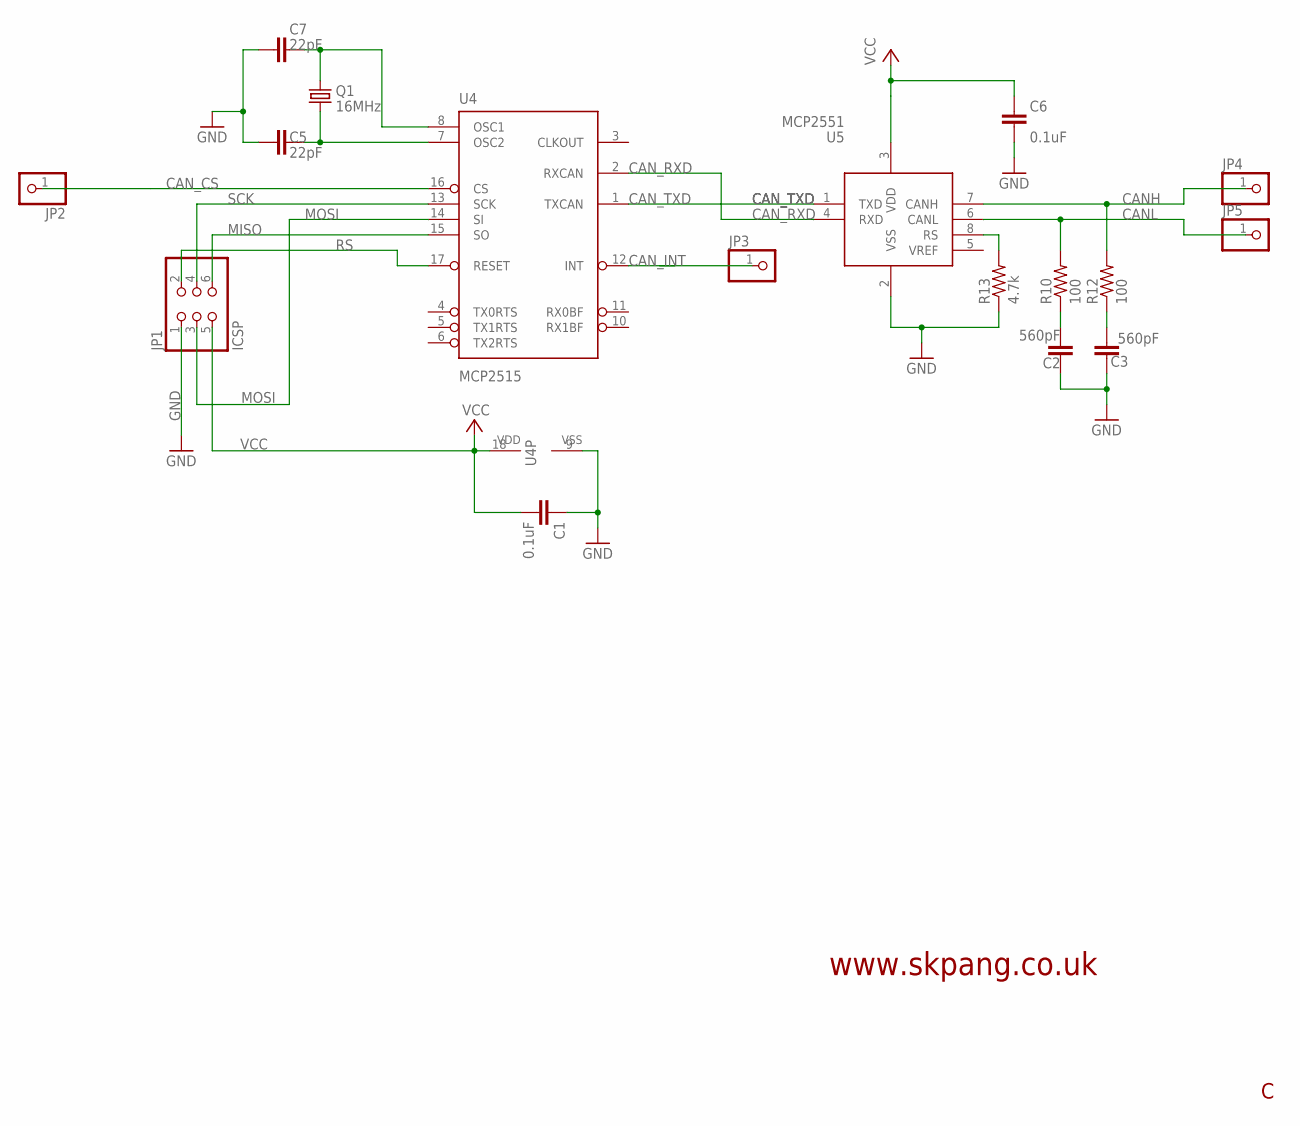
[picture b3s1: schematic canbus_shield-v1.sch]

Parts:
C1, C6: 0.1uF; 0603-CAP
C2, C3: 560pF; 0603-CAP
C5, C7: 22pF; 0603-CAP
JP1: ICSP; 2X03
JP2, JP3, JP4, JP5: PINHD-1X1; 1X01
Q1: 16MHz; CRYSTAL-SMD-5X3
R10, R12: 100; 0603-RES
R13: 4.7k; 0603-RES
U4: MCP2515; SO-18W
U5: MCP2551; SO-08M

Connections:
CANH: JP4.1, R12.2, U5.7 (CANH)
CANL: JP5.1, R10.2, U5.6 (CANL)
CAN_CS: JP2.1, U4.16 (CS)
CAN_INT: JP3.1, U4.12 (INT)
CAN_RXD: U4.2 (RXCAN), U5.4 (RXD)
CAN_TXD: U4.1 (TXCAN), U5.1 (TXD)
GND: C1.1, C2.1, C3.1, C5.1, C6.1, C7.1, JP1.1, R13.1, U4.9 (VSS), U5.2 (VSS)
MISO: JP1.6, U4.15 (SO)
MOSI: JP1.3, U4.14 (SI)
unnamed: C2.2, R10.1
unnamed: C3.2, R12.1
unnamed: R13.2, U5.8 (RS)
unnamed: C7.2, Q1.3 (2), U4.8 (OSC1)
unnamed: C5.2, Q1.1, U4.7 (OSC2)
RS: JP1.2, U4.17 (RESET)
SCK: JP1.4, U4.13 (SCK)
VCC: C1.2, C6.2, JP1.5, U4.18 (VDD), U5.3 (VDD)

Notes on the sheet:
www.skpang.co.uk

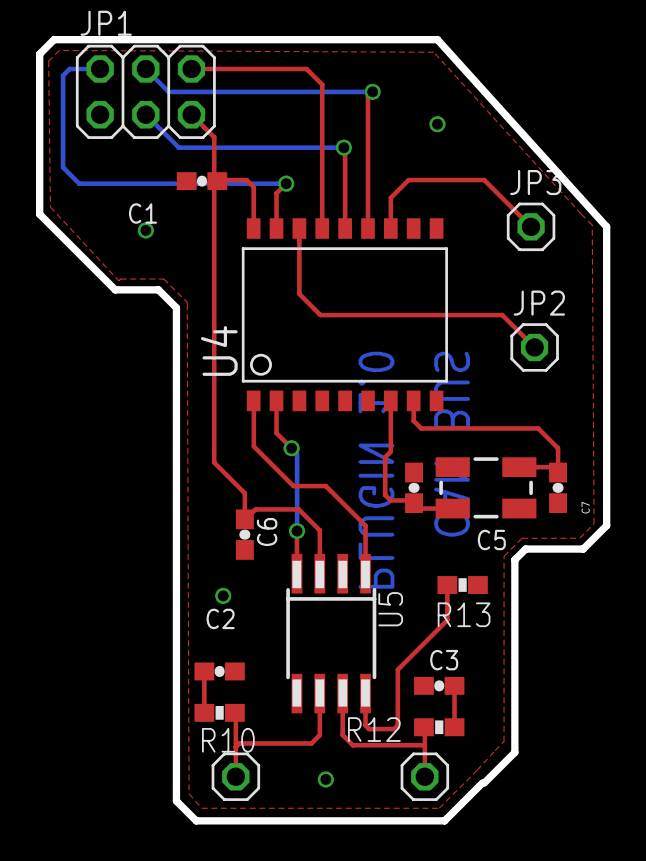
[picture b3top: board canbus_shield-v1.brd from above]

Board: 2 copper layers, 31.5 x 43.4 mm, 17 parts (0 on the bottom side), 17 nets.
